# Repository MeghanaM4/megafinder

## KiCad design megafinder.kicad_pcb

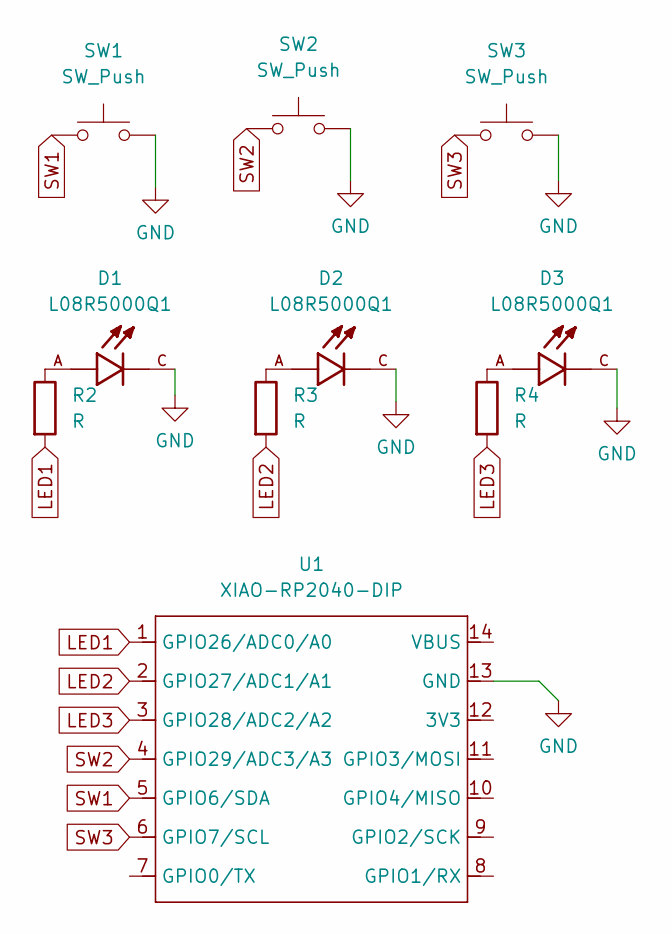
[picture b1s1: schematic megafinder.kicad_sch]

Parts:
D1, D2, D3: L08R5000Q1; LEDRD254W57D500H1070; PARTREV NA
R2, R3, R4: R; R_Axial_DIN0204_L3.6mm_D1.6mm_P5.08mm_Horizontal
SW1, SW2, SW3: SW_Push; SW_Cherry_MX_1.00u_PCB
U1: XIAO-RP2040-DIP

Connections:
GND: D1.C, D2.C, D3.C, SW1.2, SW2.2, SW3.2, U1.13 (GND)
LED1: R2.2, U1.1 (GPIO26/ADC0/A0)
LED2: R3.2, U1.2 (GPIO27/ADC1/A1)
LED3: R4.2, U1.3 (GPIO28/ADC2/A2)
unnamed: D1.A, R2.1
unnamed: D2.A, R3.1
unnamed: D3.A, R4.1
SW1: SW1.1, U1.5 (GPIO6/SDA)
SW2: SW2.1, U1.4 (GPIO29/ADC3/A3)
SW3: SW3.1, U1.6 (GPIO7/SCL)

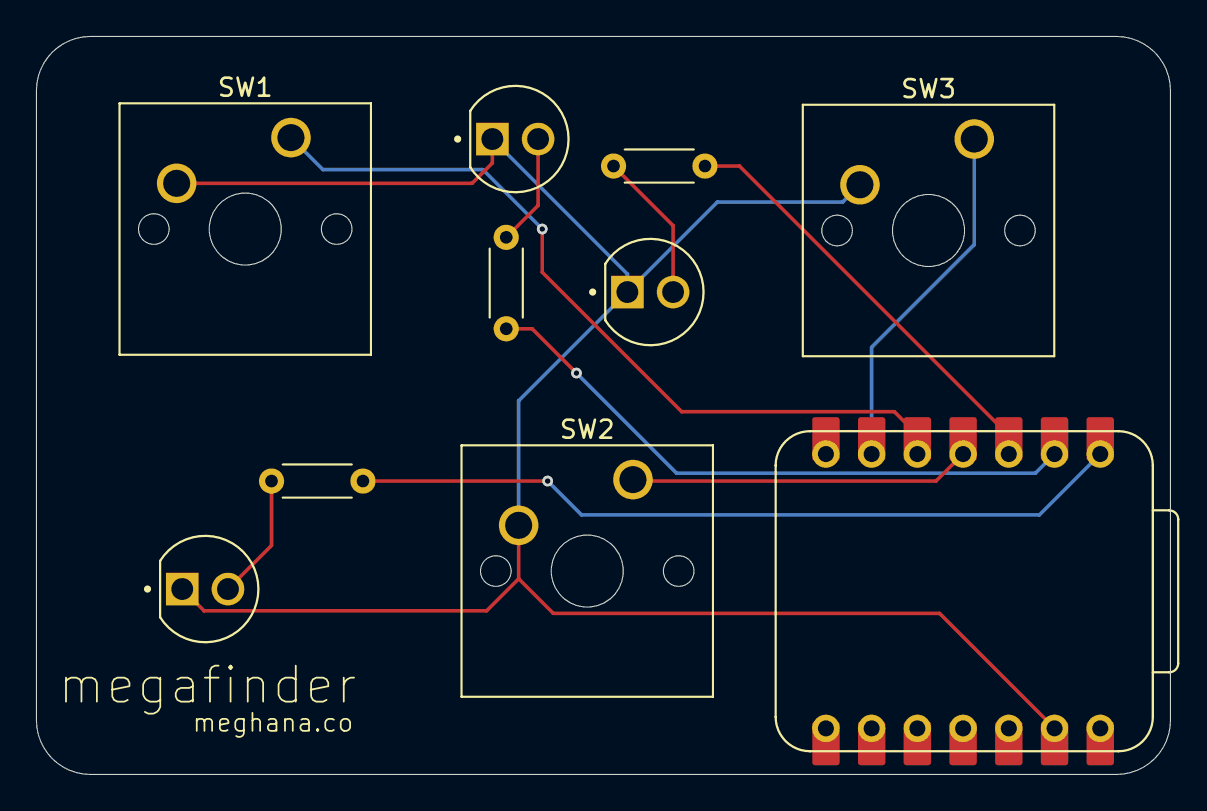
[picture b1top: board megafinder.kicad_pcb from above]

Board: 2 copper layers, 63.0 x 41.0 mm, 10 parts (0 on the bottom side), 10 nets.

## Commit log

2025-06-30 adding all my pcb progress
